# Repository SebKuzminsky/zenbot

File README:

This configuration is for the Zenbot CNC Mini Router (2007 version)
with 7i30 driver board, using the Mesa 5i23 for pwm generation &
quadrature counting.

Each axis/joint is run by a servo controlled by a 7i30.  All the servos
have no index channel, instead the index channel is used for home/limit
switches, plus the tool length offset switch.

# Spindle

The spindle is a TB-350S from Wolfgang Engineering (Richard?).

Rated for 0.0001 runout expected, 0.0004 runout max.

20,000 or 25,000 RPM, it's unclear.

Chris Radek has one, and has worked out how to replace the spindle
bearings.

# Work holding

There is not much cutting force on the work, the main job of work holding
is to keep the copper surface parallel to XY across the whole work piece.

I used Target or Scotch branch "permanent double sided tape", it seemed
to work.

FIXME: note new tape, easier to work with since it has paper backing on
one side

Chris Radek says:

    I use the thicker tape with filaments in it that's meant for making
    very poor quality installations of tile or maybe carpet?

    Duck brand "Indoor Heavy Duty Carpet Tape"

    https://www.findtape.com/shop/product-images.aspx?pid=646

Try NYC CNC's technique of "blue painter's tape/ca/blue painter's tape":
https://www.youtube.com/watch?time_continue=628&v=r6DCvtcU8_M

# Z touch off

Bring the tool down close to the work, then raise it 0.001 at a time
until you can just barely roll a precision ground dowel pin between the
tool and the work.  The pins at SSD have a diameter of 0.250 +- 0.001.

If you don't have a dowel pin, the shank of a cutter works too but make
sure you measure the actual diameter carefully.

# Speeds and Feeds

## PreciseBits RCC08-0315-026F

Fish-tail chip breaker router bit, 0.0315 diameter, 0.256 depth of cut.

Speed: 24,000
Feed: 5 ipm, 125 mm/min
Plunge feed: 2.5 ipm, 62 mm/min

https://www.precisebits.com/products/carbidebits/fcrouter.asp?product_id=713
https://www.precisebits.com/products/carbidebits/fdrouter.asp?product_id=742

## PreciseBits MN208-0100-002F

2-flute endmill, 0.010 diameter, 0.015 depth of cut.

Speed: 24,000
Feed: 2.4 ipm, 60 mm/min
Plunge feed: 1.2 ipm, 30 mm/min

https://www.precisebits.com/products/carbidebits/precisebit-stub.asp?product_id=564
https://www.precisebits.com/products/carbidebits/precisebit-stub.asp?product_id=567

## Accupro 0.010" endmill (MSC #37290426)

0.010" diameter 2-flute carbide endmill, 0.015" LOC, 1/8" Shank
Uncoated, Spiral Flute, 30° Helix, Centercutting, Right Hand Cut, Right Hand Flute

MSC prices:
    List Price $23.99
    Your Price $14.87 ea.

## Accupro 0.010" endmill (long) (MSC #37289451)

0.010" diameter 2-flute carbide endmill, 0.030" LOC, 1/8" Shank
Uncoated, Spiral Flute, 30° Helix, Centercutting, Right Hand Cut, Right Hand Flute

MSC prices:
    List Price $23.99
    Your Price $14.87 ea.

# Copper clad board

The work table can hold up to 4" x 6" boards.

I've been using MG Chemicals #506:

    Proto Board Copper Clad FR4
    Single Sided
    1 oz.
    6.00" x 4.00" (152.4mm x 101.6mm)

$7.14 from Digi-Key.

# Toolchain

KiCAD -> FlatCAM -> LinuxCNC

## KiCAD

### Schematic Capture

Design the circuit, save.

Export netlist in pcbnew format.

### PCB Layout

In the schematic editor, click the "Run Pcbnew" tool icon, or
Tools->Update PCB.

Use Mounting Hole footprints for mounting holes.

Draw the board outline on the Edge.Cuts layer.

Use "Place -> Drill and Place Offset" (or select the "place auxiliary
axis origin" tool) to set the origin of the project to the lower left
corner of the board.

To export to FlatCAM or other board fabrication tools:

    File -> Plot

        enable "Use auxiliary axis as origin"

        select the layers (B.Cu, Edge.Cuts), Plot (makes a `.gbr` gerber
        file for each layer).

        "Generate Drill Files...", enable "PTH and NPTH holes in single
        file", "Generate Drill File" (makes `.drl` file).

## FlatCAM

### Load PCB fabrication files

"Open Gerber" to load the different layers.

"Open Excellon" to load the drill file.

### Mirror the bottom copper and the drill locations

> mirror breakout-board-B.Cu.gbr -axis Y -box breakout-board-Edge.Cuts.gbr
> mirror breakout-board.drl -axis Y -box breakout-board-Edge.Cuts.gbr

### Generate trace isolation geometry from copper layer

In the Project tab, select the B.Cu object.

Switch to the Selected tab.

Set tool diameter to 0.0095" (just below 0.010" which matches the
"PreciseBits MN208-0100-002F" endmill i'm using).

Click Generate Geometry.

### Generate geometry for irregular board outlines aka Edge Cuts

In the Project tab, select the Edge.Cuts object.

Switch to the Selected tab.

Set tool diameter to 0.0315" (to match the "PreciseBits RCC08-0315-026F"
endmill i'm using for this cut).

> isolate breakout-board-Edge.Cuts.gbr -outname outline-iso
> exteriors outline-iso -outname outline
> delete outline-iso
> delete breakout-board-Edge.Cuts.gbr_iso

### Mill holes

In the Project tab, select the drill object.

Switch to the Selected tab.

Find the Mill Holes section.

Set tool diameter to 0.0315" (to match the "PreciseBits RCC08-0315-026F"
endmill i'm using for this cut).

Click Generate Geometry.

### Generate G-code

For each of the three toolpath objects (trace isolation, drill/mill, and
board outline), select the object, set Create CNC Job options, click Generate.

For the isolation job: Use the 0.010 endmill, feed 2.4, "Cut Z" should be
maybe 0.010, with a single pass.  (1 oz copper clad board has a 0.0014
inch thick copper layer, and it's pretty easy to mount the board with
less than 0.003 inch wobble.)

For the drill/mill and board outline jobs: Use the 0.031 endmill, feed
5.0, "Cut Z" should be the thickness of the board + 0.005 or so, call
it 0.070, with a depth/pass of 0.020?

### Save the G-code

In each G-code object:

* Add "G20 G64 P.0005" to "Prepend to G-code".

* Add "M2" to "Append to G-code".

* Turn off Dwell.

* Click "Export G-Code".

# FlatCAM fixes

* Actual helix milling for the holes

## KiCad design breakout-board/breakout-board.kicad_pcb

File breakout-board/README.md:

This is a breakout board for connecting the Zenbot to a Mesa FPGA board.

It connects to a standard 50-pin ribbon cable from the Mesa FPGA board.

It passes the servo pins for channels 0, 1, and 2 to a second 50-pin
connector, for connecting to the 7i30 and driving the X, Y, and Z servos.

The remaining FPGA connector pins are routed to screw terminals, for
additional IO (eg the control line for an SSR to power the spindle).

The servo control pins are:

    1-23, 29, 31, 35, 39, 43, 47 (and 49)

The GPIO pins are:

    25, 27, 33, 37, 41, 45 (and 49)

The male 50-pin connectors are TE Part #1-5499923-0

The screw terminals are Phoenix Contact Part #1725711, "MPT 0,5/ 8-2,54"

# Fabrication

1. Mount a piece of single-sided 1 oz copper clad board to the mill.
   Make sure it's level.

2. Insert a PreciseBits MN208-0100-002F cutter, touch off Z

3. Open the `outline.ngc` gcode file and touch off X and Y at the lower
   left corner of the work.

4. Safety glasses, hearing protection, and spindle on.

5. Run the `back-copper.ngc` gcode file.

6. Switch to the PreciseBits RCC08-0315-026F cutter, touch off Z but
   not X and Y.

7. Safety glasses, hearing protection, and spindle on.

8. Run `drill-mill.ngc`.

9. Run `outline.ngc`.

# Prototypes

## Prototype 0: d7a043c1

* Cut deeper!  Some of the cuts didn't remove all the copper.

* The resistor lead holes should be a little larger diameter.  The pins
  on the other four components (LED, screw terminal, 50-pin connectors)
  all fit well.

* Would it be useful to to connect the ground pins on the 50-pin
  connectors to the ground plane?

* The 2x25 connectors extend past the end of the board some.

## Prototype 1: 2033f8a4

### Design changes from previous prototype

* Use a resistor with fatter leads.

* Cut 0.010 deep instead of 0.008.

* Resize the board to be more compact, and so the 2x25 connectors fit.
  I can fit two prototypes on a 4x6 board now.

### Fabrication

Broke two 0.010 endmills while cutting `back-copper.ngc`.  The first time
I switched in a fresh tool and restarted from just before where it broke,
but that was my last spare and now the project is stalled again.

I guess the 0.010 axial depth of cut is too much, maybe make the cut in
two passes of 0.005 or so instead?

## Prototype 2: a6cbd07e

### Design changes

* Increase PCB trace isolation from 0.010" to 0.011", so i can optionally
  use larger (by 0.001, but still), cheaper endmills.

* Decrease isolation milling depth of cut from 0.010" to 0.006", hopefully
  i'll break fewer tools.  If it doesn't isolate properly (like it
  probably won't) i can always touch off Z deeper and rerun the program.

### Fabrication

First pass ran to completion, didn't break the cutter (yay!), but didn't
fully isolate the traces (as expected).

Moved Z down 0.005, reran the program.

It finished!  There were a lot of burrs on the edges of the cuts, some
that caused shorts between the traces or between the traces and the
untouched copper pour.  I scrubbed it with a scotchbrite pad and that
fixed it, it's good!

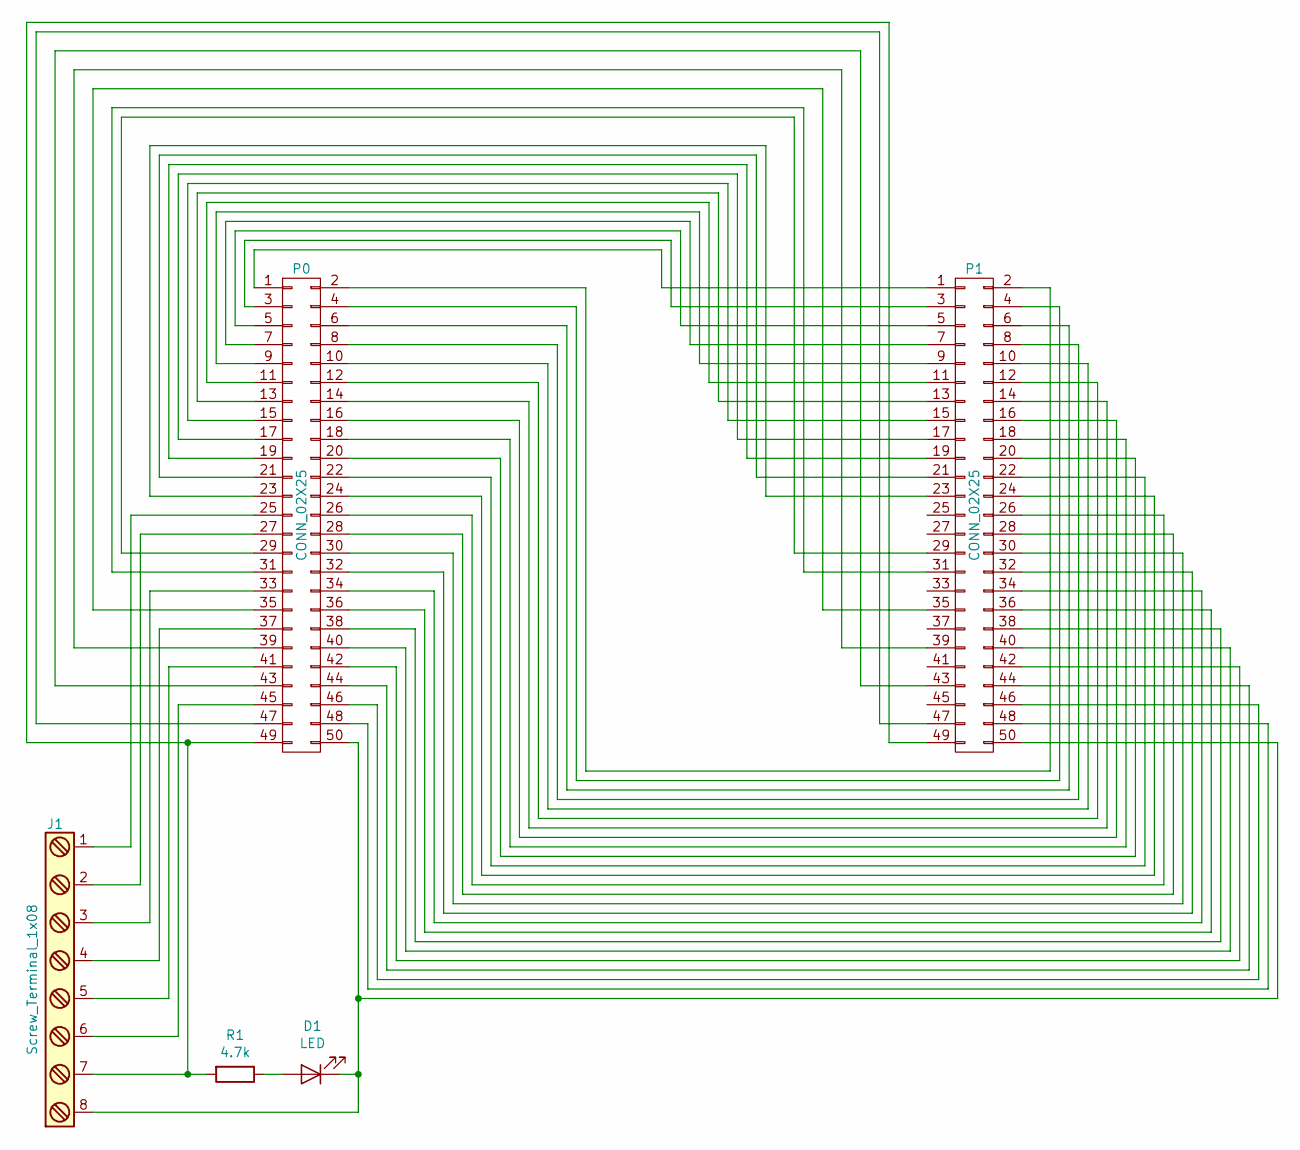
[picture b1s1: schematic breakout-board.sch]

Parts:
D1: LED; LED_D5.0mm
J1: Screw_Terminal_1x08; TerminalBlock_Phoenix_MPT-0,5-8-2.54_1x08_P2.54mm_Horizontal
P0, P1: CONN_02X25; TE-Connectivity_1-5499923-0
R1: 4.7k; R_Axial_DIN0411_L9.9mm_D3.6mm_P15.24mm_Horizontal

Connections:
unnamed: D1.1 (K), J1.8, P0.50, P1.50
unnamed: D1.2 (A), R1.1
unnamed: J1.1, P0.25
unnamed: J1.2, P0.27
unnamed: J1.3, P0.33
unnamed: J1.4, P0.37
unnamed: J1.5, P0.41
unnamed: J1.6, P0.45
unnamed: J1.7, P0.49, P1.49, R1.2
unnamed: P0.1, P1.1
unnamed: P0.2, P1.2
unnamed: P0.3, P1.3
unnamed: P0.4, P1.4
unnamed: P0.5, P1.5
unnamed: P0.6, P1.6
unnamed: P0.7, P1.7
unnamed: P0.8, P1.8
unnamed: P0.9, P1.9
unnamed: P0.10, P1.10
unnamed: P0.11, P1.11
unnamed: P0.12, P1.12
unnamed: P0.13, P1.13
unnamed: P0.14, P1.14
unnamed: P0.15, P1.15
unnamed: P0.16, P1.16
unnamed: P0.17, P1.17
unnamed: P0.18, P1.18
unnamed: P0.19, P1.19
unnamed: P0.20, P1.20
unnamed: P0.21, P1.21
unnamed: P0.22, P1.22
unnamed: P0.23, P1.23
unnamed: P0.24, P1.24
unnamed: P0.26, P1.26
unnamed: P0.28, P1.28
unnamed: P0.29, P1.29
unnamed: P0.30, P1.30
unnamed: P0.31, P1.31
unnamed: P0.32, P1.32
unnamed: P0.34, P1.34
unnamed: P0.35, P1.35
unnamed: P0.36, P1.36
unnamed: P0.38, P1.38
unnamed: P0.39, P1.39
unnamed: P0.40, P1.40
unnamed: P0.42, P1.42
unnamed: P0.43, P1.43
unnamed: P0.44, P1.44
unnamed: P0.46, P1.46
unnamed: P0.47, P1.47
unnamed: P0.48, P1.48

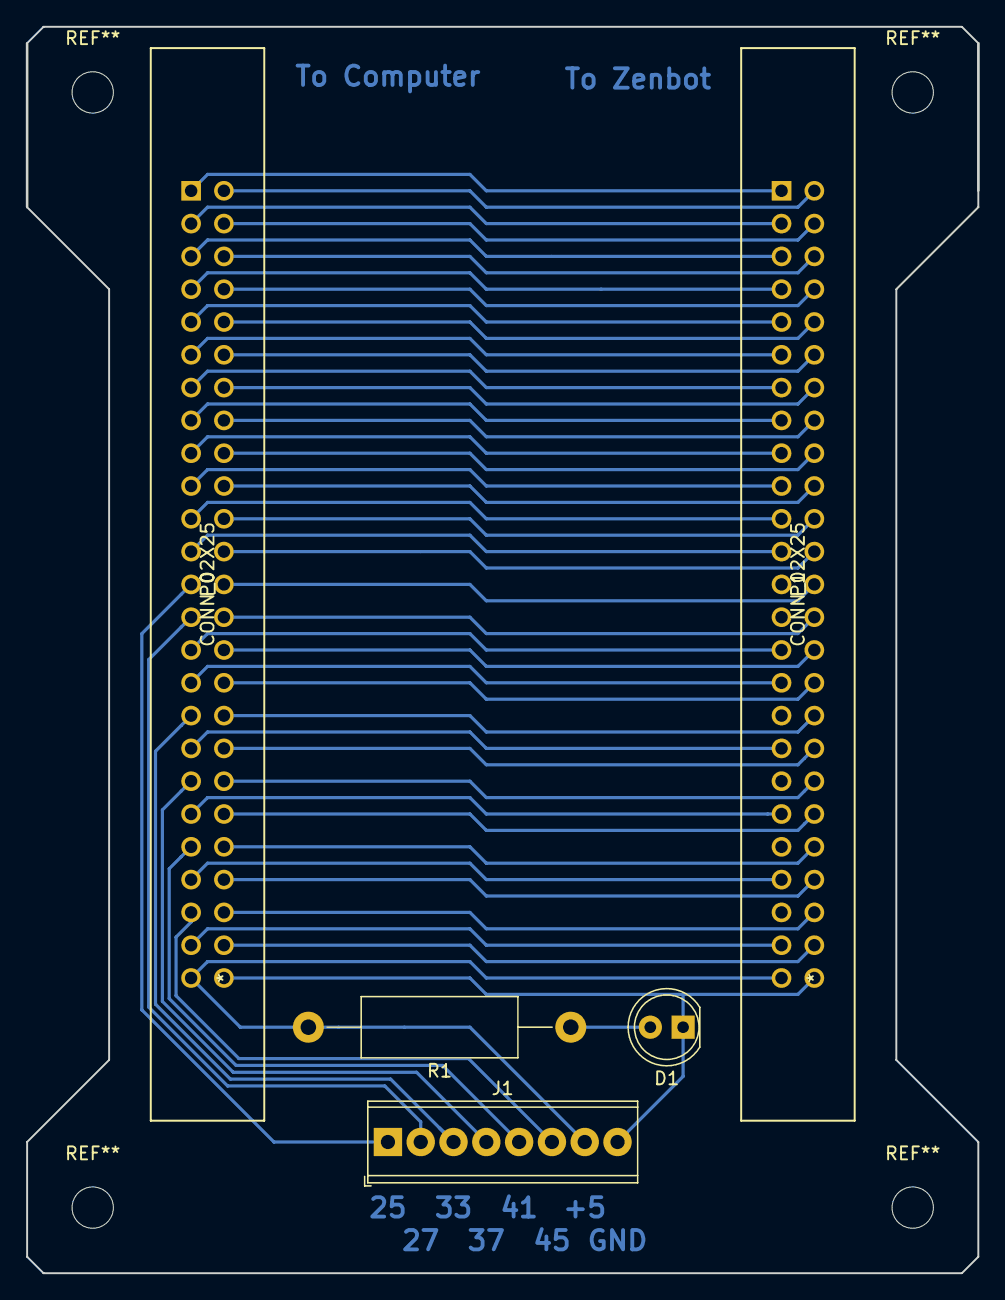
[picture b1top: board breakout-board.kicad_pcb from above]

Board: 2 copper layers, 73.7 x 96.5 mm, 5 parts (0 on the bottom side), 51 nets.

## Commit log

2007-09-14 initial
2007-12-06 for some time now, the doublestep mode has been activated by just setting stepspace to 0
    setting stepgen accel limits may improve behavior a bit
2008-05-17 configuration to use pluto-step
2008-05-17 name is clearer
2008-05-17 enables are nice
2008-06-02 switch over to pluto -- whee, it works
2008-07-02 * correct for measured backlash * remove jogwheel setup, that board seems to have died
2008-07-02 those jogs are too long
2008-07-05 It's total overkill, but now I'm using a servo motor with encoder attached to an m5i20 as the jog wheel.
2008-07-16 for Y limit switch installed at rear of table
2008-07-17 homing for Y switch near front of table
2008-07-20 tool length sensor
2008-08-02 ignore these files
2008-08-02 don't track these files
2008-08-02 notes
2008-08-02 hackishly use mesa index inputs for homing
2008-08-07 restore backlash. add X, Y home switches
2008-08-13 fix jog slider limits. machine has started stalling at 1.2ipm, wtf
2008-08-14 switches now independent
2008-08-14 no need for 3 different periods. oh and no discernable benefit from 2kHz servo rate either
2008-08-14 those comments weren't doing anyone any good
2008-08-14 obsessively line up items
2008-08-14 I don't envision going back to software step generation
2008-08-16 g30 for dremel
2008-08-16 g30 for tool length sensor with new spindle
2008-08-16 extended Z travel with new sensor
2008-09-01 spindle control and manual toolchange
2008-09-01 stepper-mpg
2008-09-01 re-measure backlash. tool change position. stepper mpg
2008-09-04 some notes I've been taking
2008-09-04 some datasheets that it is useful to refer to
2008-09-04 it's nice to have velocity and accel to scope
2008-09-04 changed spindle mounting which moved the TLS again
2008-09-05 new datasheet
2008-09-07 tweak homing velocity. commented velocities were stable in testing
    .. but after a few thousand inches of tests, I noticed a bunch of metal
    shavings made from the same material as the nuts (brass?) so maybe going
    this fast is what they call a bad idea. I can't wait to get these screws
    and nuts replaced!
2008-09-15 more notes
2008-09-15 switching to ribbon cable for switch terminal board caused pin numbers to change
2008-09-16 additional measurements
2008-09-18 new screws and nuts
2008-09-20 limits are a bit bigger without those collars
2008-09-20 describe accessible area of table in terms of the mounting holes in the table
2008-10-08 datasheet for pancake servos
2008-10-10 switch datasheet
2008-10-10 some drawings and boss gcode files used to mill a replacement part for the zenbot
2008-10-11 Z home switch
2009-01-15 disable home switch until wiring can be made permanent
2009-01-20 the future is mesa
2009-01-29 make it work again after some system changes
    * m5i20 removed
    * rewired
    * added Z switch again
2009-05-21 old xylotex datasheet
2009-05-22 rev1 board to adapt to xylotex
2009-05-22 convert to 5i20
2009-05-22 pinout of mesa-xylotex converter
2009-05-22 rev1 board as milled
2009-05-22 swap axes around according to my temporary wiring
2009-05-22 temporarily disable home switches
2009-05-23 set pins to open drain to avoid ringing on rising edges
2009-05-23 continue hooking stuff back up
2009-05-23 saw a stall on X, lower all the limits a bit
2009-06-19 new datasheets
2009-07-05 boss gcode for motor mount
2009-07-07 make spindle work
2009-07-07 stepper stuff
2009-07-07 keep G28/G30 home in git, not other parameters
2009-07-07 ludicrous speed
2009-07-07 eagle backup files
2009-07-07 continued tuning
2009-07-11 a useful script to run one motor around
2009-07-11 a generated file that shouldn't get history
2009-07-11 this is useful
2009-07-21 3-axis motion
2009-07-27 include specialized component source
2009-08-20 moved to first connector
2009-08-20 make homing work again
2009-08-20 get rid of whitespace
2010-05-28 enlarge buffer
2010-05-28 correct feeds
2010-05-28 useful for testing, not strictly related to zenbot
2010-05-28 some kind of exercise script?
2010-05-28 some kind of test script
2010-05-28 exercise the axes
2010-05-28 use a firmware with probe latch
2010-05-28 firmware with probe latch
2018-11-03 remove redundant pin settings
2018-11-03 update README and TODO
2018-11-03 more to do
2018-11-03 switch zenbot.ini to new 5i23 hal config, make it load on 2.7
2018-11-05 get rid of [AXIS_*](INSTANCE)
2018-11-06 move xy home switch to input 005
2018-11-06 slow everything down so it stops f-erroring
    This lets us home the machine so we can start tuning the servos.
2018-11-07 todo: config confusion
2018-11-07 ini: better jog increments
2018-11-07 ini: add a [TRAJ]POSITION_FILE
2018-11-07 ini: fix Y and Z limits
2018-11-07 ini: tweak X pid tuning
2018-11-07 ini: home Y faster
2018-11-07 git ignore the new position.txt file
2018-11-07 todo: more work on the spindle
2018-11-07 readme: add info on spindle
2018-11-14 ini: change editor to gvim
2018-11-14 ini: don't set [DISPLAY]MAX_VELOCITY, just use [TRAJ]
2018-11-14 all axes run the splash g-code, Y and Z still need tuning
2018-11-21 tweaked splash g-code for a 0.032" endmill
2018-11-21 minor additions to README & TODO
2018-11-21 start adding a breakout board
2018-11-22 README: add notes on work holding
2018-11-22 more work on the breakout board
2018-11-25 save breakout-board from kicad 4.0
2018-11-25 update breakout board for kicad 5.0, add gerber & drill files
2018-11-26 add proper mounting holes
2018-11-28 README: add notes on Z touch-off and F & S
2018-11-28 start adding notes on the toolchain
2018-11-28 compactify, add edge cuts, merge all drilled holes (plated and non-plated)
2018-11-28 README: fix feeds & speeds
2018-11-28 README: fix plunge feed for 0.032 endmill
2018-11-28 README: add depth-of-cut info to tools
2018-11-28 lots of notes on how to use flatcam
2018-11-28 g-code!
2018-12-02 todo: more stuff needed
2018-12-03 todo: more to do
2018-12-03 ini: tune Z min limit
2018-12-03 ini: tune Z home velocities
2018-12-03 ini: decrease Z max accel for reliability
    I should really tune the Y and Z PID loops
2018-12-03 bought some dowel pins for the SSD Zenbot
2018-12-07 README: add another workholding technique to try
2019-03-24 README: fix typos
2019-03-30 todo: add a vacuum port
2019-03-30 zenbot: add 1.000" jog increment
2019-03-30 zenbot: make Z a little slower, avoid following errors
2019-03-30 zenbot: update PROGRAM_PREFIX for my home dir
2019-03-30 add o-sub to present the work
2019-03-31 add datasheet for spindle SSR
2019-03-31 README: more notes on FlatCAM
2019-03-31 zenbot: slow down max speed a bit
2019-03-31 breakout-board: add notes on fabrication, & need to cut deeper
2019-04-06 todo: added notes on SSR
2019-04-06 breakout-board: added notes on the prototype i made
2019-04-08 add footprint for 2x25 connector
2019-04-08 README: add a reminder to document the new tape
2019-04-08 README: better notes on KiCAD
2019-04-08 README: better notes on FlatCAM
2019-04-08 breakout-board: next prototype is ready
2019-04-12 breakout-board: fix a copy/paste error
2019-04-12 breakout-board: failed to cut the board, again
2019-04-12 README: add links to endmills
2019-04-12 todo: bought the allen wrench
2019-04-12 todo: start notes on a custom cabinet/workbench
2019-04-12 breakout-board: rework for lerger cutter, shallower DOC
2019-05-07 README: add info on MSC endmills & MG Chemicals copper-clad board
2019-05-08 breakout board README: note which commits the prototypes were made from
2019-05-08 breakout-board: prototype 2 back-copper looks good!
2019-05-15 README is in MarkDown
2019-05-15 README markdown syntax fixes
2019-05-15 README: more markdown fixes
2019-07-30 README: add more info on pcb layout and flatcam
2019-07-30 better flatcam settings & process
2019-08-14 better breakout-board README
2019-08-14 breakout-board README: fix a bug in XY touchoff
2019-08-14 better flatcam instructions in readme
2019-08-14 better FlatCAM setup instructions
2019-08-14 README: better FlatCAM instructions
2019-08-14 better FlatCAM info in README
2019-08-14 add another flatcam fix
2020-01-29 add notes on the O-rings used as spindle drive belts
2020-03-23 README: add some S&F info from Kyocera
2021-07-17 README: update feeds & speeds info
2021-07-17 README: start section on how to use FlatCAM 8.994 BETA (wip)
2021-07-17 README: add more info on the copper-clad board
2021-07-17 README: more work on the FlatCAM 8.994 instructions
2021-07-18 README: note issues with new FlatCAM config
2021-07-18 render README.md to html
2021-07-18 cache S&F info from Kyocera
2021-07-18 README: move copper clad board info up
2021-07-18 README: organize tool/speed&feed info better
2021-07-18 README: reorg s&f info
2021-07-24 README: fix md syntax for urls
2021-07-24 README: add price info for some cutters
